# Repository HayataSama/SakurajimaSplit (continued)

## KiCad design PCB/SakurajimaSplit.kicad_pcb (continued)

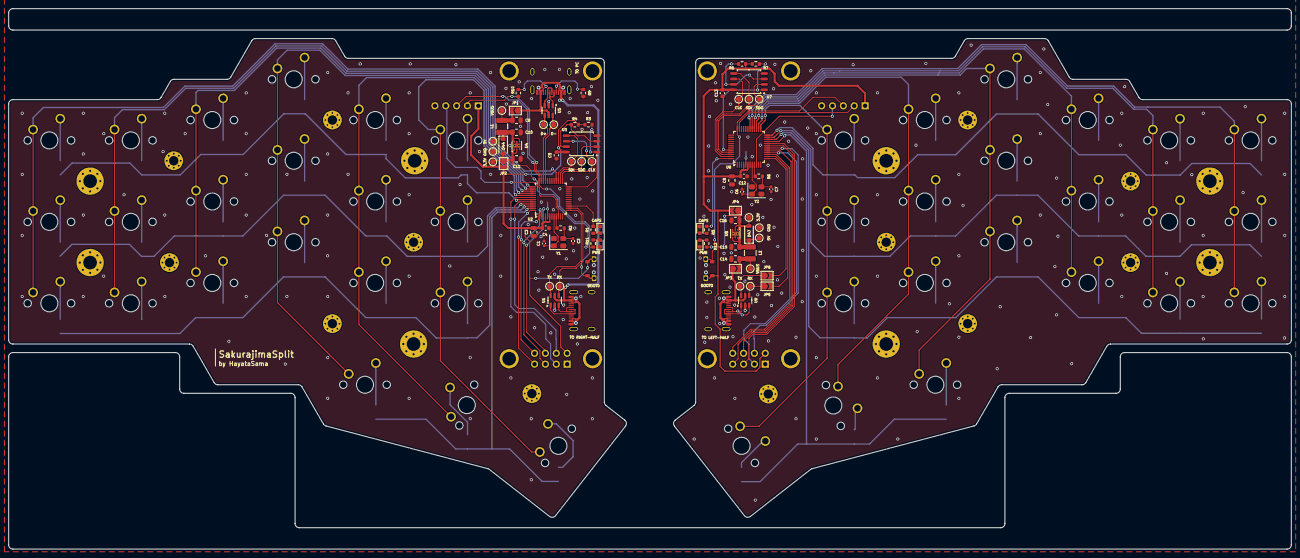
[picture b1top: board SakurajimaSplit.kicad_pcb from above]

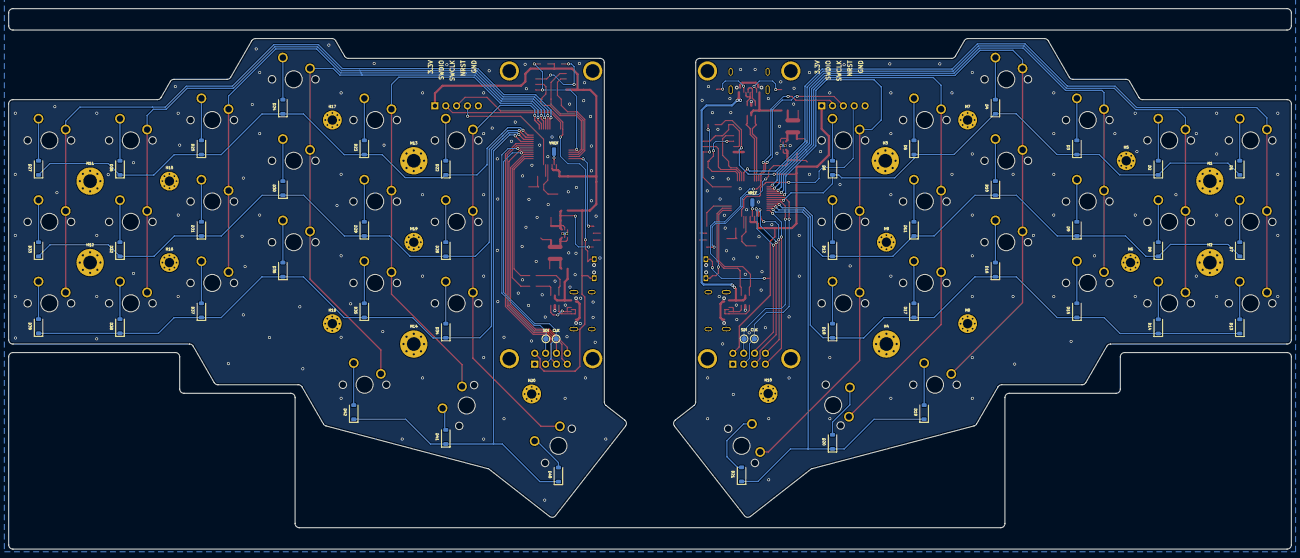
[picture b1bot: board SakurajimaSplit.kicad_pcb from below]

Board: 2 copper layers, 300.0 x 126.4 mm, 192 parts (70 on the bottom side), 128 nets.

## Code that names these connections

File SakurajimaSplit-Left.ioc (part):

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Mcu.Name=STM32G0B1C(B-C-E)Tx
Mcu.Package=LQFP48
Mcu.UserName=STM32G0B1CBTx
PA11\ [PA9].GPIOParameters=GPIO_Label
PA11\ [PA9].GPIO_Label=USB_D-
PA11\ [PA9].Mode=Device
PA11\ [PA9].Signal=USB_DM
PA12\ [PA10].GPIOParameters=GPIO_Label
PA12\ [PA10].GPIO_Label=USB_D+
PA12\ [PA10].Mode=Device
PA12\ [PA10].Signal=USB_DP
PA13.GPIOParameters=GPIO_Label
PA13.GPIO_Label=SWDIO
PA13.Mode=Serial_Wire
PA13.Signal=SYS_SWDIO
PA14-BOOT0.GPIOParameters=GPIO_Label
PA14-BOOT0.GPIO_Label=SWCLK/BOOT0
PA14-BOOT0.Mode=Serial_Wire
PA14-BOOT0.Signal=SYS_SWCLK
PA15.GPIOParameters=GPIO_Label
PA15.GPIO_Label=COL1
PA15.Signal=GPIO_Output
PA2.GPIOParameters=GPIO_Label
PA2.GPIO_Label=USART_TX
PA2.Mode=Asynchronous
PA2.Signal=USART2_TX
PA3.GPIOParameters=GPIO_Label
PA3.GPIO_Label=USART_RX
PA3.Mode=Asynchronous
PA3.Signal=USART2_RX
PA4.GPIOParameters=GPIO_Label
PA4.GPIO_Label=CapsLock
PA4.Signal=GPIO_Output
PA8.GPIOParameters=GPIO_Label
PA8.GPIO_Label=COL0
PA8.Signal=GPIO_Output
PB12.GPIOParameters=GPIO_Label
PB12.GPIO_Label=Flash_CS
PB12.Signal=GPIO_Output
PB13.GPIOParameters=GPIO_Label
PB13.GPIO_Label=Flash_SCLK
PB13.Mode=Full_Duplex_Master
PB13.Signal=SPI2_SCK
PB14.GPIOParameters=GPIO_Label
PB14.GPIO_Label=Flash_SDO
PB14.Mode=Full_Duplex_Master
PB14.Signal=SPI2_MISO
PB15.GPIOParameters=GPIO_Label
PB15.GPIO_Label=Flash_SDI
PB15.Mode=Full_Duplex_Master
PB15.Signal=SPI2_MOSI
PB3.GPIOParameters=GPIO_Label
PB3.GPIO_Label=Display_SCLK
PB3.Mode=Simplex_Bidirectional_Master
PB3.Signal=SPI1_SCK
PB4.GPIOParameters=GPIO_Label
PB4.GPIO_Label=ROW0
PB4.Signal=GPIO_Input
PB5.GPIOParameters=GPIO_Label
PB5.GPIO_Label=Display_SDI
PB5.Mode=Simplex_Bidirectional_Master
PB5.Signal=SPI1_MOSI
PB6.GPIOParameters=GPIO_Label
PB6.GPIO_Label=ROW1
PB6.Signal=GPIO_Input
PB7.GPIOParameters=GPIO_Label
PB7.GPIO_Label=ROW2
PB7.Signal=GPIO_Input
PB8.GPIOParameters=GPIO_Label
PB8.GPIO_Label=ROW3
PB8.Signal=GPIO_Input
PB9.GPIOParameters=GPIO_Label
PB9.GPIO_Label=Display_CS
PB9.Signal=GPIO_Output
PC13.GPIOParameters=GPIO_Label
PC13.GPIO_Label=Display_EN
PC13.Signal=GPIO_Output
PC14-OSC32_IN\ (PC14).GPIOParameters=GPIO_Label
PC14-OSC32_IN\ (PC14).GPIO_Label=Display_RST
PC14-OSC32_IN\ (PC14).Signal=GPIO_Output
PC15-OSC32_OUT\ (PC15).GPIOParameters=GPIO_Label
PC15-OSC32_OUT\ (PC15).GPIO_Label=Display_DC
PC15-OSC32_OUT\ (PC15).Signal=GPIO_Output
PD0.GPIOParameters=GPIO_Label
PD0.GPIO_Label=COL2
PD0.Signal=GPIO_Output
PD1.GPIOParameters=GPIO_Label
PD1.GPIO_Label=COL3
PD1.Signal=GPIO_Output
PD2.GPIOParameters=GPIO_Label
PD2.GPIO_Label=COL4
PD2.Signal=GPIO_Output
PD3.GPIOParameters=GPIO_Label
PD3.GPIO_Label=COL5
PD3.Signal=GPIO_Output
PF0-OSC_IN\ (PF0).GPIOParameters=GPIO_Label
PF0-OSC_IN\ (PF0).GPIO_Label=HSE_IN
PF0-OSC_IN\ (PF0).Mode=HSE-External-Oscillator
PF0-OSC_IN\ (PF0).Signal=RCC_OSC_IN
PF1-OSC_OUT\ (PF1).GPIOParameters=GPIO_Label
PF1-OSC_OUT\ (PF1).GPIO_Label=HSE_OUT
PF1-OSC_OUT\ (PF1).Mode=HSE-External-Oscillator
PF1-OSC_OUT\ (PF1).Signal=RCC_OSC_OUT
PF2-NRST.GPIOParameters=GPIO_Label
PF2-NRST.GPIO_Label=NRST
PF2-NRST.Signal=GPIO_Input
RCC.HSE_VALUE=8000000
RCC.SYSCLKFreq_VALUE=64000000
RCC.SYSCLKSource=RCC_SYSCLKSOURCE_PLLCLK
board=custom

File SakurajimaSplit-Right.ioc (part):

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Mcu.Name=STM32G0B1C(B-C-E)Tx
Mcu.Package=LQFP48
Mcu.UserName=STM32G0B1CBTx
PA13.GPIOParameters=GPIO_Label
PA13.GPIO_Label=SWDIO
PA13.Mode=Serial_Wire
PA13.Signal=SYS_SWDIO
PA14-BOOT0.GPIOParameters=GPIO_Label
PA14-BOOT0.GPIO_Label=SWCLK/BOOT0
PA14-BOOT0.Mode=Serial_Wire
PA14-BOOT0.Signal=SYS_SWCLK
PA2.GPIOParameters=GPIO_Label
PA2.GPIO_Label=USART_TX
PA2.Mode=Asynchronous
PA2.Signal=USART2_TX
PA3.GPIOParameters=GPIO_Label
PA3.GPIO_Label=USART_RX
PA3.Mode=Asynchronous
PA3.Signal=USART2_RX
PA4.GPIOParameters=GPIO_Label
PA4.GPIO_Label=Display_EN
PA4.Signal=GPIO_Output
PA5.GPIOParameters=GPIO_Label
PA5.GPIO_Label=Display_SCLK
PA5.Mode=Simplex_Bidirectional_Master
PA5.Signal=SPI1_SCK
PA6.GPIOParameters=GPIO_Label
PA6.GPIO_Label=Display_CS
PA6.Signal=GPIO_Output
PA7.GPIOParameters=GPIO_Label
PA7.GPIO_Label=Display_SDI
PA7.Mode=Simplex_Bidirectional_Master
PA7.Signal=SPI1_MOSI
PA8.GPIOParameters=GPIO_Label
PA8.GPIO_Label=COL3
PA8.Signal=GPIO_Output
PA9.GPIOParameters=GPIO_Label
PA9.GPIO_Label=COL4
PA9.Signal=GPIO_Output
PB0.GPIOParameters=GPIO_Label
PB0.GPIO_Label=Display_DC
PB0.Signal=GPIO_Output
PB1.GPIOParameters=GPIO_Label
PB1.GPIO_Label=Display_RST
PB1.Signal=GPIO_Output
PB10.GPIOParameters=GPIO_Label
PB10.GPIO_Label=ROW2
PB10.Signal=GPIO_Input
PB11.GPIOParameters=GPIO_Label
PB11.GPIO_Label=ROW1
PB11.Signal=GPIO_Input
PB12.GPIOParameters=GPIO_Label
PB12.GPIO_Label=ROW0
PB12.Signal=GPIO_Input
PB13.GPIOParameters=GPIO_Label
PB13.GPIO_Label=COL0
PB13.Signal=GPIO_Output
PB14.GPIOParameters=GPIO_Label
PB14.GPIO_Label=COL1
PB14.Signal=GPIO_Output
PB15.GPIOParameters=GPIO_Label
PB15.GPIO_Label=COL2
PB15.Signal=GPIO_Output
PB2.GPIOParameters=GPIO_Label
PB2.GPIO_Label=ROW3
PB2.Signal=GPIO_Input
PB5.GPIOParameters=GPIO_Label
PB5.GPIO_Label=Flash_CS
PB5.Signal=GPIO_Output
PB6.GPIOParameters=GPIO_Label
PB6.GPIO_Label=Flash_SDO
PB6.Mode=Full_Duplex_Master
PB6.Signal=SPI2_MISO
PB7.GPIOParameters=GPIO_Label
PB7.GPIO_Label=Flash_SDI
PB7.Mode=Full_Duplex_Master
PB7.Signal=SPI2_MOSI
PB8.GPIOParameters=GPIO_Label
PB8.GPIO_Label=Flash_SCLK
PB8.Mode=Full_Duplex_Master
PB8.Signal=SPI2_SCK
PB9.GPIOParameters=GPIO_Label
PB9.GPIO_Label=CapsLock
PB9.Signal=GPIO_Output
PC6.GPIOParameters=GPIO_Label
PC6.GPIO_Label=COL5
PC6.Signal=GPIO_Output
PF0-OSC_IN\ (PF0).GPIOParameters=GPIO_Label
PF0-OSC_IN\ (PF0).GPIO_Label=HSE_IN
PF0-OSC_IN\ (PF0).Mode=HSE-External-Oscillator
PF0-OSC_IN\ (PF0).Signal=RCC_OSC_IN
PF1-OSC_OUT\ (PF1).GPIOParameters=GPIO_Label
PF1-OSC_OUT\ (PF1).GPIO_Label=HSE_OUT
PF1-OSC_OUT\ (PF1).Mode=HSE-External-Oscillator
PF1-OSC_OUT\ (PF1).Signal=RCC_OSC_OUT
PF2-NRST.GPIOParameters=GPIO_Label
PF2-NRST.GPIO_Label=NRST
PF2-NRST.Signal=GPIO_Input
RCC.HSE_VALUE=8000000
RCC.SYSCLKFreq_VALUE=64000000
RCC.SYSCLKSource=RCC_SYSCLKSOURCE_PLLCLK
board=custom

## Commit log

2025-05-21 init
2025-05-22 chore: setup project structure
    update .gitignore to exclude kicad related temp files
    add project license
2025-05-22 feat(schematic): basic circuitry for the mcu
2025-05-22 feat(schematic): add key matrix
2025-06-27 feat(sch): add host USB connection and power circuit
2025-06-28 feat(sch): add USB to right-half circuit
2025-06-28 feat(sch): add rotary encoder
2025-06-29 feat(sch): add symbol and footprint for ssd1305 oled display module
2025-06-29 feat(sch): add OLED display
2025-07-01 feat(sch): mcu connections, test points and schematic cleanup
2025-08-09 docs: add lcd dimensions, mcu pinout, KLE layout and some notes
2025-08-10 feat(sch): cleanup and anotate schematic, choose components
    - Fixed mistakes in schematic
    - Anotated the schematic
    - Found and chose components
    - Added GND test points
    - Ran ERC and fixed all errors and warnings
2025-08-10 feat(sch): design right half of the keyboard
2025-08-10 fix(sch): fix ERC errors regarding power flags
2025-08-10 feat(pcb): assign all footprints
2025-08-10 fix(sch): fix matrix diode designators not starting from 1
2025-08-11 feat(pcb): setup board and define manufacturing constraints
2025-08-11 feat(pcb): add missing 3d models
2025-08-11 feat(pcb): add temporary OLED module 3d model
2025-09-16 feat(sch): add spi flash, remove rotary encoder, fix footprints
2025-09-16 fix(sch): remove encoder net labels, update mountinghole footprints
2025-09-16 fix(sch): swap LEDs with their series resistors
2025-09-16 fix(sch): fix wrong footprint for MX21 & MX40
2025-09-16 feat(pcb): new kle layout
2025-09-18 feat(pcb): design rough layout and update schematic accordingly
2025-09-25 feat(pcb): finish designing rough layout and update schematic
    - Removed unused MCU pads
    - Removed some GND testpoints
    - Updated MCU connections based on PCB layout and MCU orientation
    - Updated key matrix layout for a less aggressive one which feels more
    comfortable and more visually pleasing
    - Re-annotated schematic
2025-09-25 feat(pcb): fine tune pcb layout
    - fine tuned pcb layout
    - swaped TX and RX pins of right half for better routing
2025-09-26 feat(pcb): route left half
2025-09-27 feat(pcb): route right half
2025-09-28 fix(pcb): fix DRC errors, fix silkscreen, fix some routing
2025-09-29 feat(pcb): add mounting holes, fix some bugs
2025-09-30 feat(pcb): add stitching vias
2025-09-30 feat(pcb): add teardrops
2025-10-01 fix(pcb): fix teardrops, routing, silkscreen
2025-10-01 feat(pcb): add mousebites and finish pcb panel
2025-10-02 fix(pcb): fix a mousebite, fix fab layer
2025-10-02 fix(pcb): fix swd header placement, fix revision silkscreen
2025-10-03 feat(pcb): add Mai and Sakuta silkscreen
2025-10-04 fix(pcb): fix some inconsistencies before manufacturing
2026-05-11 chore: update readme
2026-05-11 chore: update gitignore
2026-05-11 feat(mech): add final CAD model of the case
2026-05-11 chore: add a few pics from the 3D models
2026-05-11 feat: add manufacturing files
2026-05-11 chore: update README
    Fix some typos
    Add new photos
